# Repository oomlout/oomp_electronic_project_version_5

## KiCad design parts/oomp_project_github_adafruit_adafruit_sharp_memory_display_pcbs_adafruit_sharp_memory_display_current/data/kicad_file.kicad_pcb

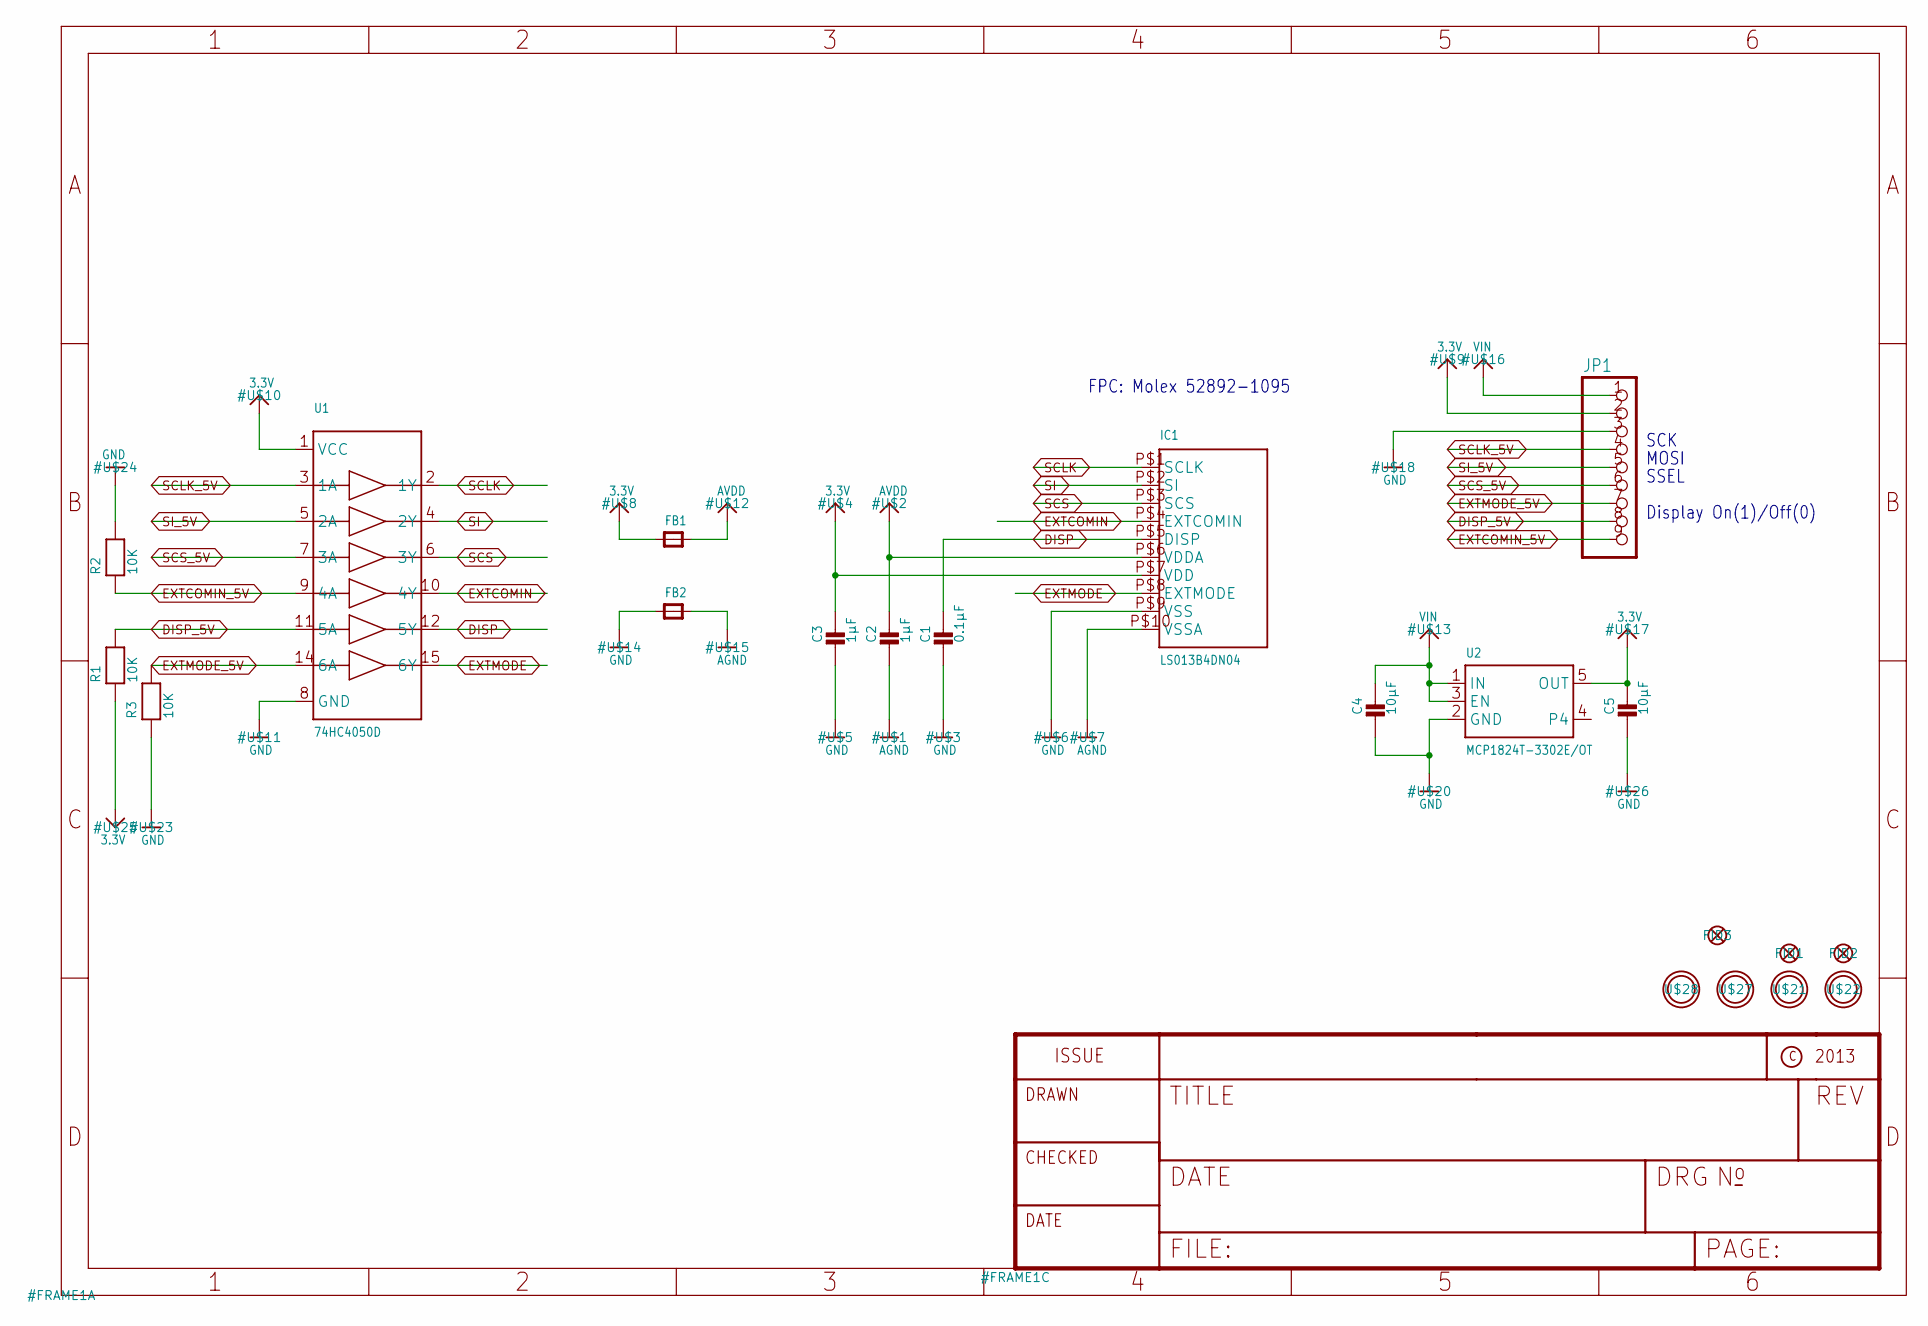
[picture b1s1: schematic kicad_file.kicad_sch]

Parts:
C1: 0.1µF; _0805
C2, C3: 1µF; _0805
C4, C5: 10µF; _0805
FB1, FB2: FERRITE_0805; _0805
FID1, FID2, FID3: FIDUCIAL""; FIDUCIAL_1MM
IC1: LS013B4DN04; FPC_10PIN_52892-1095
JP1: HEADER-1X970MIL; 1X09_ROUND_70
R1, R2, R3: 10K; _0805
U1: 74HC4050D; SOIC16
U2: MCP1824T-3302E/OT; SOT23-5
U$21, U$22, U$27, U$28: MOUNTINGHOLE3.0THIN; MOUNTINGHOLE_3.0_PLATEDTHIN

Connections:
3.3V: C3.1, C5.1, FB1.1, IC1.P$7 (VDD), JP1.2, R1.1, U1.1 (VCC), U2.5 (OUT)
AGND: C2.2, FB2.2, IC1.P$10 (VSSA)
AVDD: C2.1, FB1.2, IC1.P$6 (VDDA)
DISP: C1.1, IC1.P$5 (DISP), U1.12 (5Y)
DISP_5V: JP1.8, R1.2, U1.11 (5A)
EXTCOMIN: IC1.P$4 (EXTCOMIN), U1.10 (4Y)
EXTCOMIN_5V: JP1.9, R2.1, U1.9 (4A)
EXTMODE: IC1.P$8 (EXTMODE), U1.15 (6Y)
EXTMODE_5V: JP1.7, R3.2, U1.14 (6A)
GND: C1.2, C3.2, C4.2, C5.2, FB2.1, IC1.P$9 (VSS), JP1.3, R2.2, R3.1, U1.8 (GND), U2.2 (GND)
SCLK: IC1.P$1 (SCLK), U1.2 (1Y)
SCLK_5V: JP1.4, U1.3 (1A)
SCS: IC1.P$3 (SCS), U1.6 (3Y)
SCS_5V: JP1.6, U1.7 (3A)
SI: IC1.P$2 (SI), U1.4 (2Y)
SI_5V: JP1.5, U1.5 (2A)
VIN: C4.1, JP1.1, U2.1 (IN), U2.3 (EN)

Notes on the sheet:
MOSI
SSEL
FPC: Molex 52892-1095
SCK
Display On(1)/Off(0)

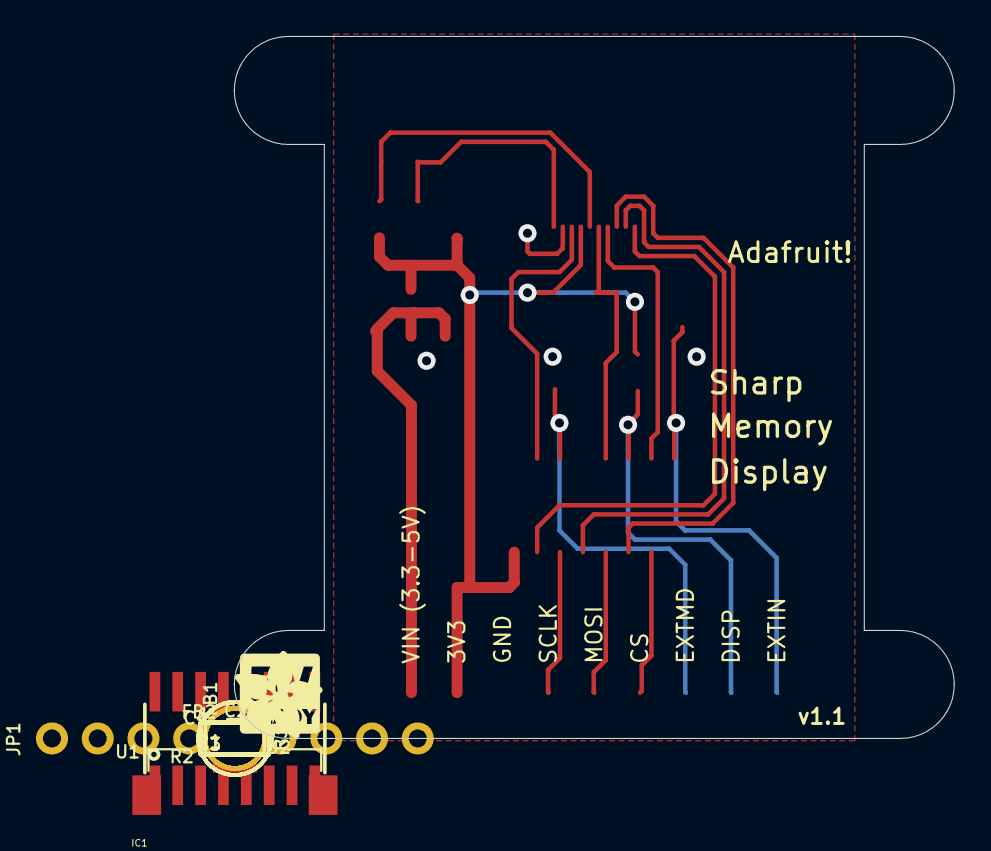
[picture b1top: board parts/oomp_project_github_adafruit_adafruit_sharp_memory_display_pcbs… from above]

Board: 16 copper layers, 40.0 x 39.0 mm, 23 parts (0 on the bottom side), 17 nets.

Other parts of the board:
U$19: LOGIC_5VREADY_5MM
U$29: ADAFRUIT_5MM

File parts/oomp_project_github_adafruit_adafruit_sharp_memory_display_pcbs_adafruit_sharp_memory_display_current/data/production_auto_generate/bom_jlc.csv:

Comment,Designator,Footprint,LCSC Part #
,JP1,Adafruit_SharpMemoryDisplay-import-fps:1X09_ROUND_70,C2932701
,"FB1,FB2",Adafruit_SharpMemoryDisplay-import-fps:_0805,
,U$29,Adafruit_SharpMemoryDisplay-import-fps:ADAFRUIT_5MM,
,U$19,Adafruit_SharpMemoryDisplay-import-fps:LOGIC_5VREADY_5MM,
0.1µF,C1,Adafruit_SharpMemoryDisplay-import-fps:_0805,
10K,"R1,R2,R3",Adafruit_SharpMemoryDisplay-import-fps:_0805,C17414
10µF,"C4,C5",Adafruit_SharpMemoryDisplay-import-fps:_0805,
1µF,"C2,C3",Adafruit_SharpMemoryDisplay-import-fps:_0805,
74HC4050D,U1,Adafruit_SharpMemoryDisplay-import-fps:SOIC16,
LS013B4DN04,IC1,Adafruit_SharpMemoryDisplay-import-fps:FPC_10PIN_52892-1095,
MCP1824T-3302E/OT,U2,Adafruit_SharpMemoryDisplay-import-fps:SOT23-5,

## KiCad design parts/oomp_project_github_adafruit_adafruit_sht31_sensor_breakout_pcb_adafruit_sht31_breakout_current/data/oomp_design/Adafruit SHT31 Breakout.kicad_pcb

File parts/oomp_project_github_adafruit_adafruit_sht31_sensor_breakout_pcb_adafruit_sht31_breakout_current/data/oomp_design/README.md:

# OOMP KiCad design copy

Open `Adafruit SHT31 Breakout.kicad_pro` (or the `.kicad_pcb` / `.kicad_sch`) in KiCad. Local OOMP libraries are under `libraries/`. Original inputs are preserved in [../original/](../original/).

Only verified unchanged installed KiCad defaults were renamed. Modified, custom, unmatched and unavailable items remain unchanged. Soldering variants are never swapped during conversion. Existing pad coordinates, nets and UUIDs are preserved.

See [conversion_report.yaml](conversion_report.yaml) for every conversion and skip. Copy this directory before editing; regeneration refuses to overwrite edited design files.

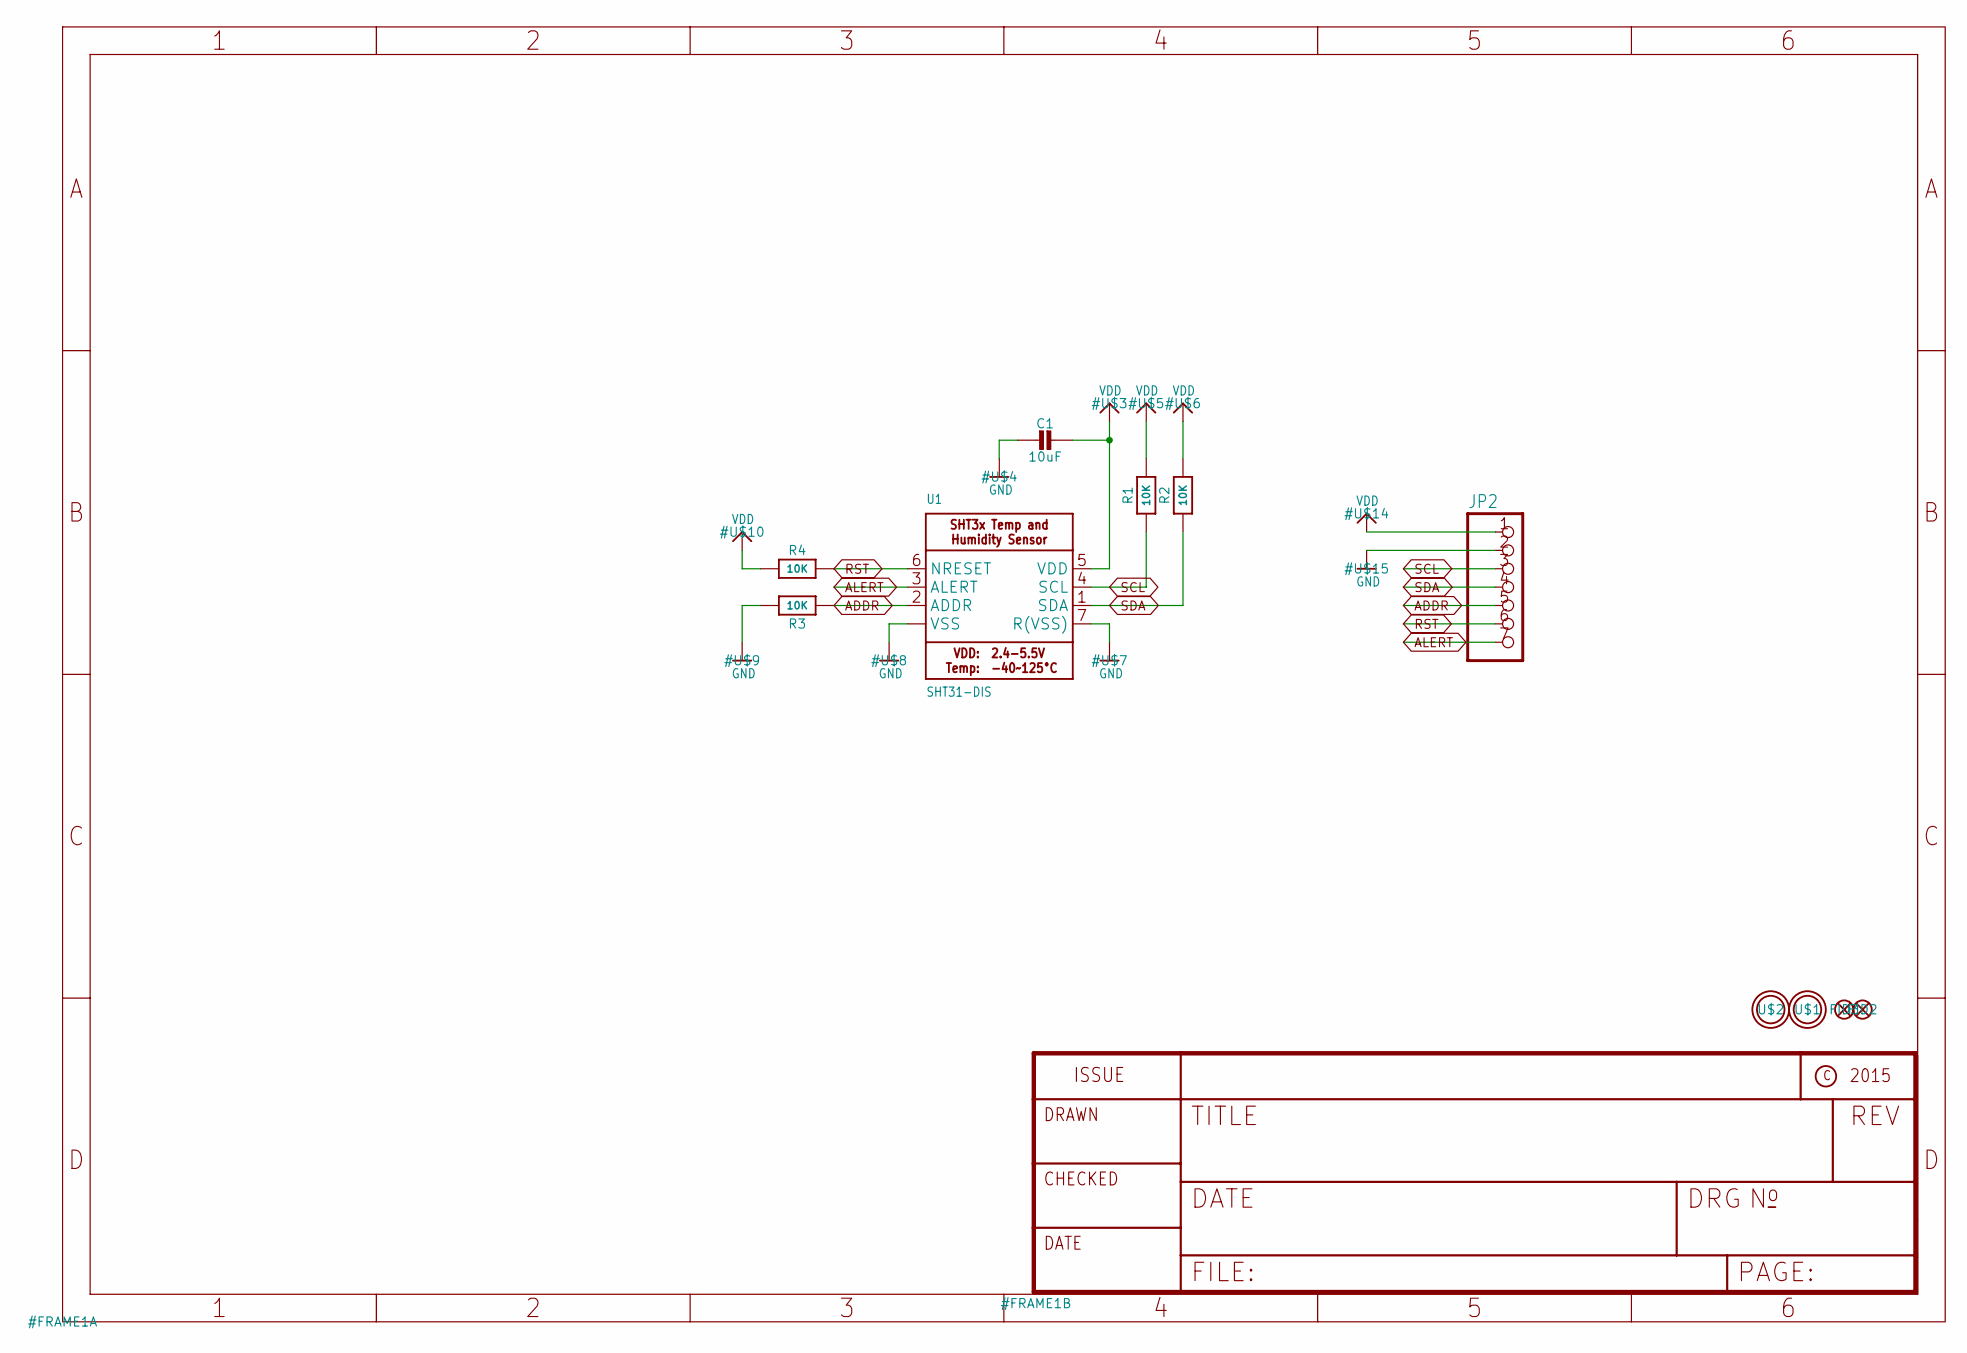
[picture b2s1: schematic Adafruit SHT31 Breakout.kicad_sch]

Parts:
C1: 10uF; 0805-NO
FID2, FID3: FIDUCIAL""; FIDUCIAL_1MM
JP2: HEADER-1X770MIL; 1X07_ROUND_70
R1, R2, R4: 10K; 0805-NO
R3: 10K; _0805MP
U1: SHT31-DIS; SHT3X
U$1, U$2: MOUNTINGHOLE2.5; MOUNTINGHOLE_2.5_PLATED

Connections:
ADDR: JP2.5, R3.1, U1.2 (ADDR)
ALERT: JP2.7, U1.3 (ALERT)
GND: C1.2, JP2.2, R3.2, U1.7 (R(VSS)), U1.8 (VSS), U1.THERMAL (VSS)
RST: JP2.6, R4.2, U1.6 (NRESET)
SCL: JP2.3, R1.1, U1.4 (SCL)
SDA: JP2.4, R2.1, U1.1 (SDA)
VDD: C1.1, JP2.1, R1.2, R2.2, R4.1, U1.5 (VDD)

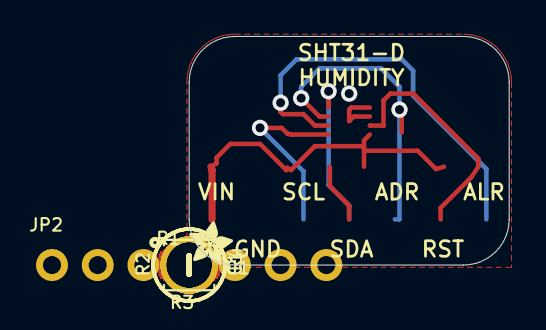
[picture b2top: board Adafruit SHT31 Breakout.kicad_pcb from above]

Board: 2 copper layers, 17.8 x 12.7 mm, 13 parts (1 on the bottom side), 7 nets.

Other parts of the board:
U$11: PCBFEAT-REV-040
U$13: ADAFRUIT_2.5MM

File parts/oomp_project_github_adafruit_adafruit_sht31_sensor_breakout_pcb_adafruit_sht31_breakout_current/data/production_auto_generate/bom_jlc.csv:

Comment,Designator,Footprint,LCSC Part #
,JP2,Adafruit SHT31 Breakout-import-fps:1X07_ROUND_70,C7501585
,U$13,Adafruit SHT31 Breakout-import-fps:ADAFRUIT_2.5MM,
,U$11,Adafruit SHT31 Breakout-import-fps:PCBFEAT-REV-040,
10K,"R1,R2,R4",Adafruit SHT31 Breakout-import-fps:0805-NO,C17414
10K,R3,Adafruit SHT31 Breakout-import-fps:_0805MP,C17414
10uF,C1,Adafruit SHT31 Breakout-import-fps:0805-NO,
SHT31-DIS,U1,Adafruit SHT31 Breakout-import-fps:SHT3X,

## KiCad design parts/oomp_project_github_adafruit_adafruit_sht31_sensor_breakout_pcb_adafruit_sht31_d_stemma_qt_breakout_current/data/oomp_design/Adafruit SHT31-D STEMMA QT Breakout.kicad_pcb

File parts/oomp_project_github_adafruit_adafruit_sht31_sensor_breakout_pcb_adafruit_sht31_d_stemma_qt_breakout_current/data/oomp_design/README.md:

# OOMP KiCad design copy

Open `Adafruit SHT31-D STEMMA QT Breakout.kicad_pro` (or the `.kicad_pcb` / `.kicad_sch`) in KiCad. Local OOMP libraries are under `libraries/`. Original inputs are preserved in [../original/](../original/).

Only verified unchanged installed KiCad defaults were renamed. Modified, custom, unmatched and unavailable items remain unchanged. Soldering variants are never swapped during conversion. Existing pad coordinates, nets and UUIDs are preserved.

See [conversion_report.yaml](conversion_report.yaml) for every conversion and skip. Copy this directory before editing; regeneration refuses to overwrite edited design files.

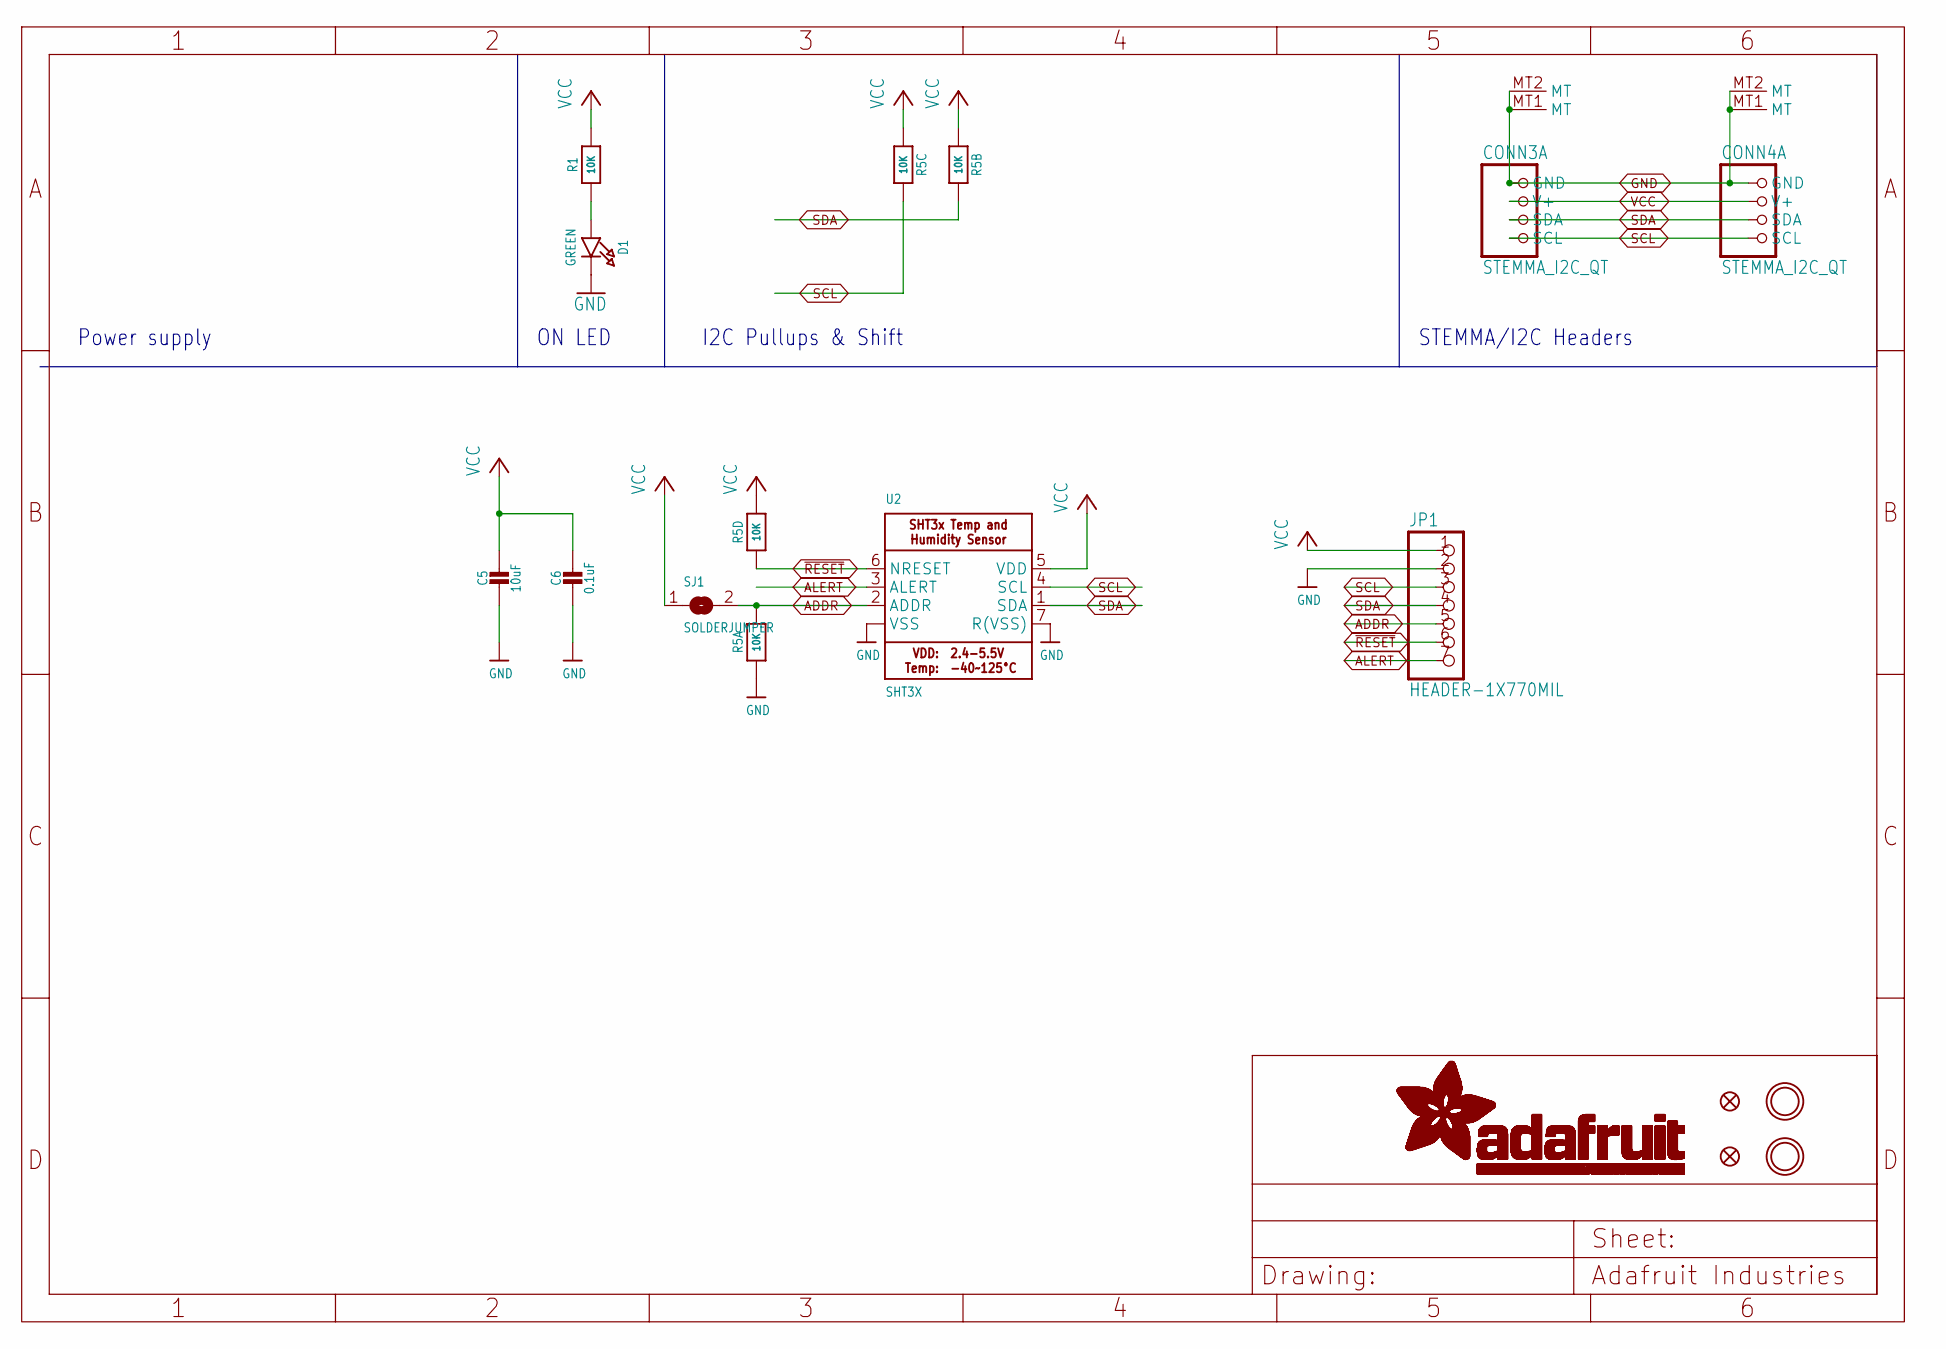
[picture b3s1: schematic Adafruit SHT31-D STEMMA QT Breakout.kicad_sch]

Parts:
C5: 10uF; 0805-NO
C6: 0.1uF; 0603-NO
CONN3, CONN4: STEMMA_I2C_QT; JST_SH4
D1: GREEN; CHIPLED_0603_NOOUTLINE
FID3, FID4: FIDUCIAL_1MM
JP1: HEADER-1X770MIL; 1X07_ROUND_70
R1: 10K; 0603-NO
R5: 10K; RESPACK_4X0603
SJ1: SOLDERJUMPER; SOLDERJUMPER_ARROW_NOPASTE
U2: SHT3X
U$19, U$20: MOUNTINGHOLE2.5; MOUNTINGHOLE_2.5_PLATED

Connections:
ADDR: JP1.5, R5.8 (2), SJ1.2, U2.2 (ADDR)
ALERT: JP1.7, U2.3 (ALERT)
GND: C5.2, C6.2, CONN3.1 (GND), CONN3.MT1 (MT), CONN3.MT2 (MT), CONN4.1 (GND), CONN4.MT1 (MT), CONN4.MT2 (MT), D1.C, JP1.2, R5.1, U2.7 (R(VSS)), U2.8 (VSS), U2.THERMAL (VSS)
unnamed: D1.A, R1.1
SCL: CONN3.4 (SCL), CONN4.4 (SCL), JP1.3, R5.6 (2), U2.4 (SCL)
SDA: CONN3.3 (SDA), CONN4.3 (SDA), JP1.4, R5.7 (2), U2.1 (SDA)
VCC: C5.1, C6.1, CONN3.2 (V+), CONN4.2 (V+), JP1.1, R1.2, R5.2 (1), R5.3 (1), R5.5 (2), SJ1.1, U2.5 (VDD)
~RESET: JP1.6, R5.4 (1), U2.6 (NRESET)

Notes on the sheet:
STEMMA/I2C Headers
Power supply
I2C Pullups & Shift
ON LED

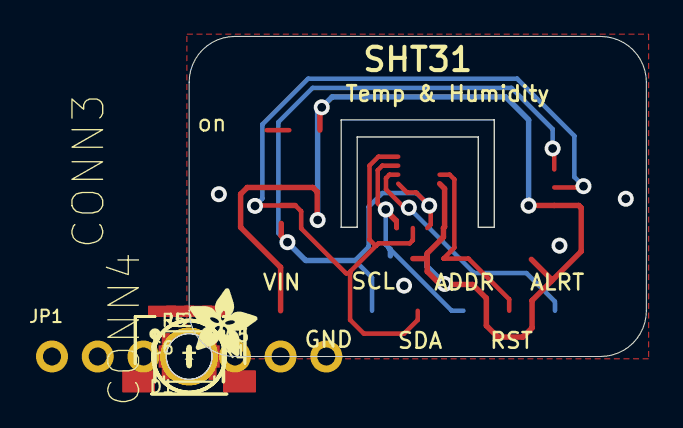
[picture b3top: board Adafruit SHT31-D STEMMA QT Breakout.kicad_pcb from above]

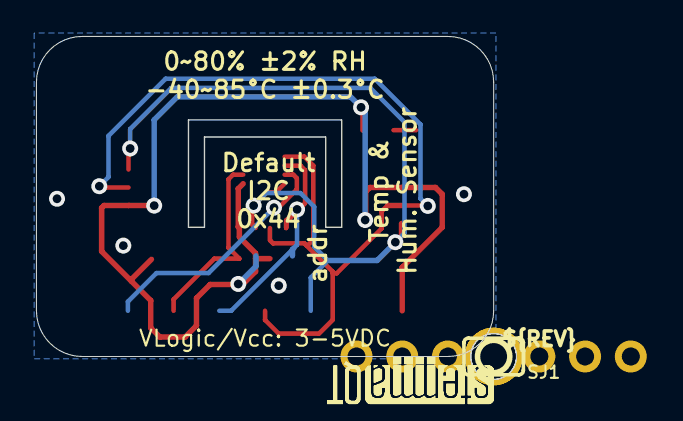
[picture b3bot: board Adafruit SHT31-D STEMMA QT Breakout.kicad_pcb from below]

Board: 2 copper layers, 25.4 x 17.8 mm, 20 parts (4 on the bottom side), 8 nets.

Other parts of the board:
U$28: ADAFRUIT_3.5MM
U$29: PCBFEAT-REV-040
U$30, U$31: STEMMAQT
UNK_HOLE_0: dummyfp0
UNK_HOLE_1: dummyfp1

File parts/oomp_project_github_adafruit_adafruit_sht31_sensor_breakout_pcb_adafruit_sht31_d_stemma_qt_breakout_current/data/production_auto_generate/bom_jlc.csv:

Comment,Designator,Footprint,LCSC Part #
,JP1,Adafruit SHT31-D STEMMA QT Breakout-import-fps:1X07_ROUND_70,C7501585
,U$28,Adafruit SHT31-D STEMMA QT Breakout-import-fps:ADAFRUIT_3.5MM,
,U$29,Adafruit SHT31-D STEMMA QT Breakout-import-fps:PCBFEAT-REV-040,
,U2,Adafruit SHT31-D STEMMA QT Breakout-import-fps:SHT3X,
,"U$30,U$31",Adafruit SHT31-D STEMMA QT Breakout-import-fps:STEMMAQT,
0.1uF,C6,Adafruit SHT31-D STEMMA QT Breakout-import-fps:0603-NO,C14663
10K,R1,Adafruit SHT31-D STEMMA QT Breakout-import-fps:0603-NO,C98220
10K,R5,Adafruit SHT31-D STEMMA QT Breakout-import-fps:RESPACK_4X0603,C98220
10uF,C5,Adafruit SHT31-D STEMMA QT Breakout-import-fps:0805-NO,
GREEN,D1,Adafruit SHT31-D STEMMA QT Breakout-import-fps:CHIPLED_0603_NOOUTLINE,
STEMMA_I2C_QT,"CONN3,CONN4",Adafruit SHT31-D STEMMA QT Breakout-import-fps:JST_SH4,C160404

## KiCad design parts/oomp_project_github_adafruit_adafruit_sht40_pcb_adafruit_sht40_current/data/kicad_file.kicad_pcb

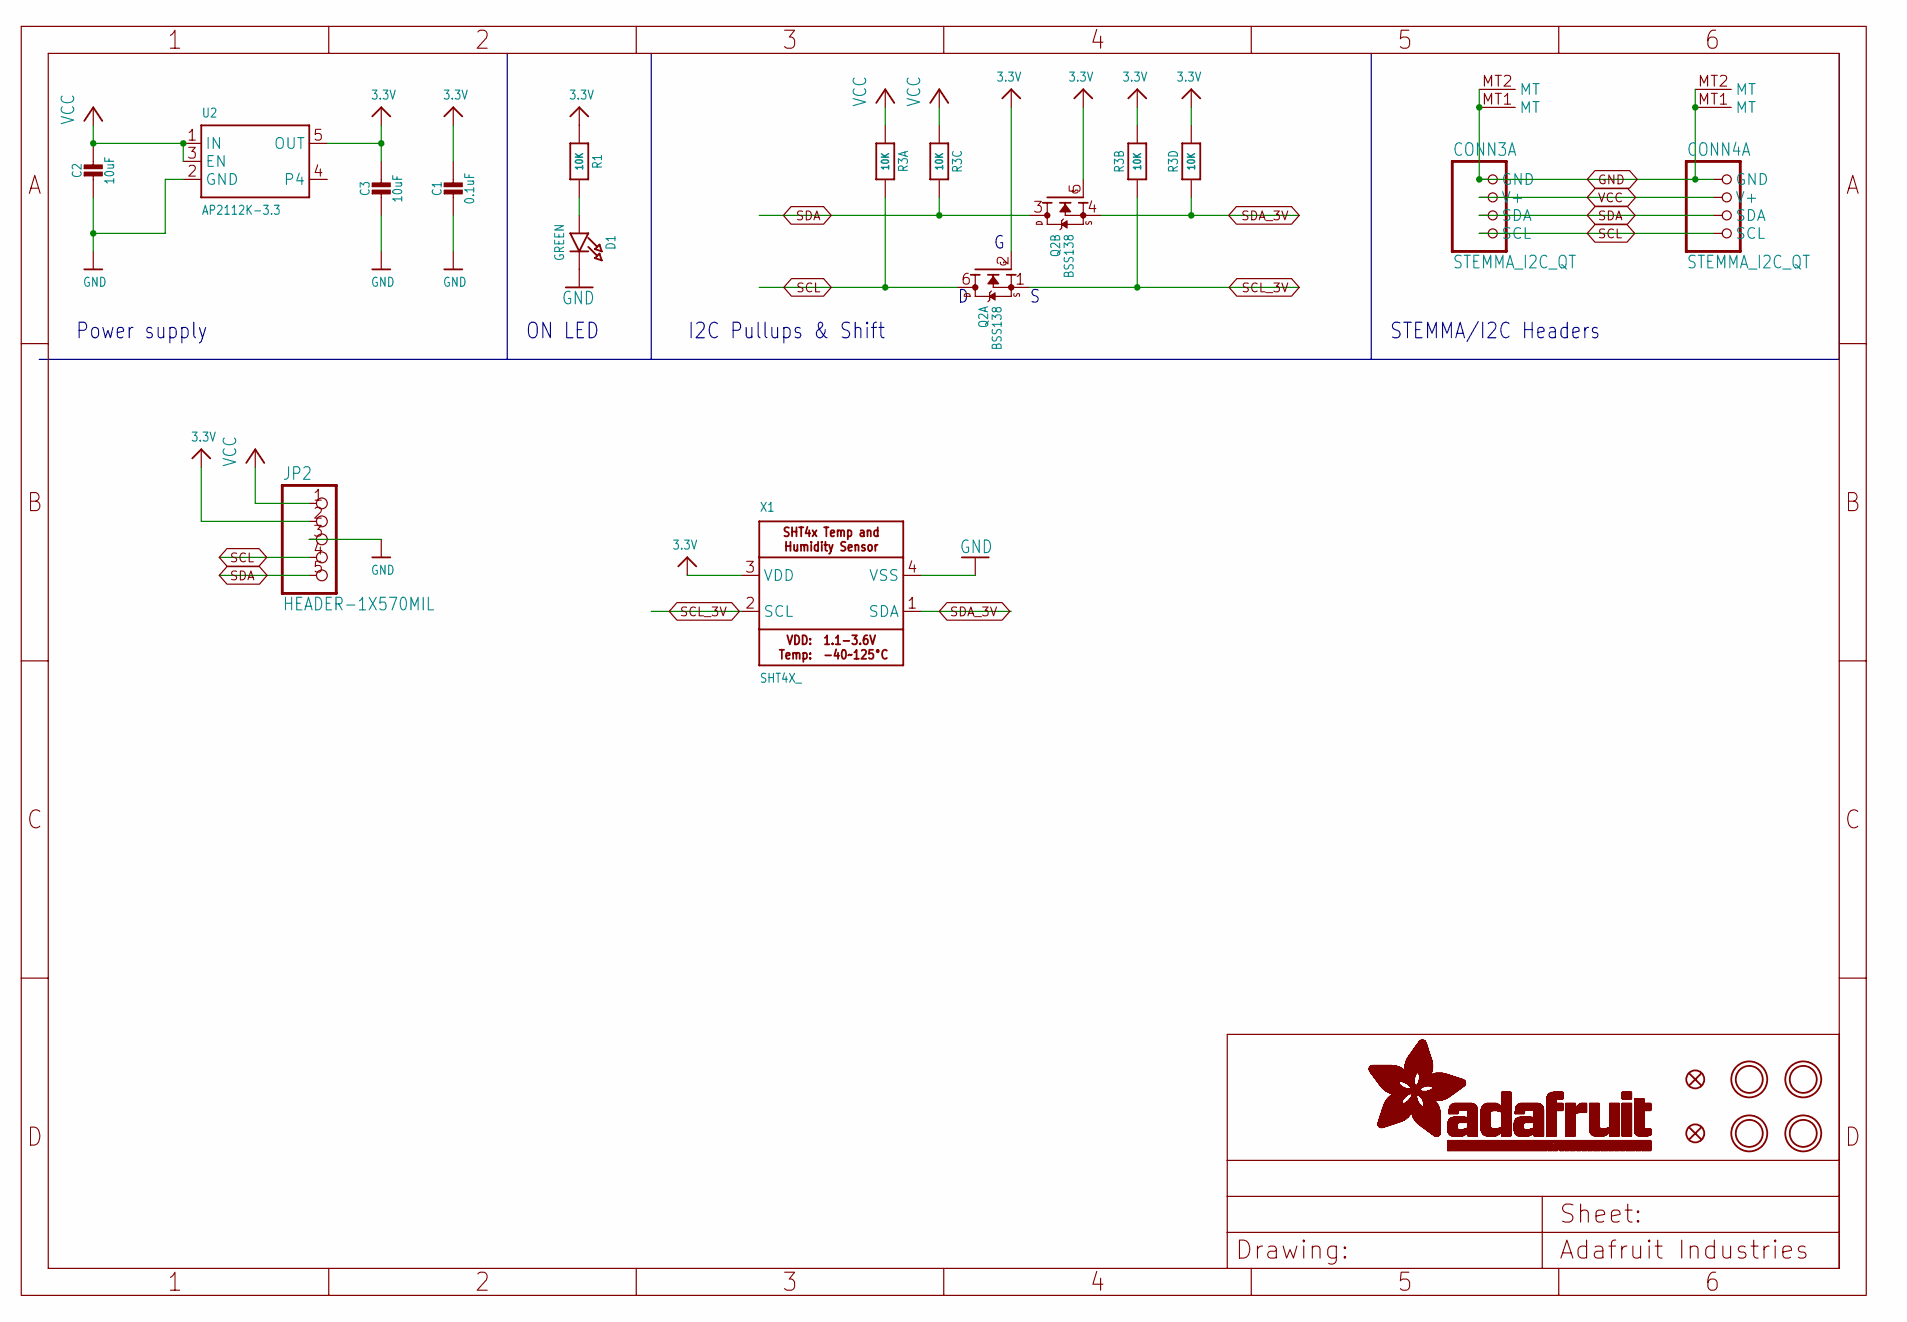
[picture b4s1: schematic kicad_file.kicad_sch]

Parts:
C1: 0.1uF; 0603-NO
C2, C3: 10uF; 0805-NO
CONN3, CONN4: STEMMA_I2C_QT; JST_SH4
D1: GREEN; CHIPLED_0603_NOOUTLINE
FID3, FID4: FIDUCIAL_1MM
JP2: HEADER-1X570MIL; 1X05_ROUND_70
Q2: BSS138; SOT363
R1: 10K; 0603-NO
R3: 10K; RESPACK_4X0603
U2: AP2112K-3.3; SOT23-5
U$1, U$17, U$19, U$21: MOUNTINGHOLE2.5; MOUNTINGHOLE_2.5_PLATED
X1: SHT4X_; SHT4X

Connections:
3.3V: C1.1, C3.1, JP2.2, Q2.2 (G), Q2.5 (G), R1.1, R3.2 (1), R3.4 (1), U2.5 (OUT), X1.3 (VDD)
GND: C1.2, C2.2, C3.2, CONN3.1 (GND), CONN3.MT1 (MT), CONN3.MT2 (MT), CONN4.1 (GND), CONN4.MT1 (MT), CONN4.MT2 (MT), D1.C, JP2.3, U2.2 (GND), X1.4 (VSS)
unnamed: D1.A, R1.2
SCL: CONN3.4 (SCL), CONN4.4 (SCL), JP2.4, Q2.6 (D), R3.8 (2)
SCL_3V: Q2.1 (S), R3.7 (2), X1.2 (SCL)
SDA: CONN3.3 (SDA), CONN4.3 (SDA), JP2.5, Q2.3 (D), R3.6 (2)
SDA_3V: Q2.4 (S), R3.5 (2), X1.1 (SDA)
VCC: C2.1, CONN3.2 (V+), CONN4.2 (V+), JP2.1, R3.1, R3.3 (1), U2.1 (IN), U2.3 (EN)

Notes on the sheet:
STEMMA/I2C Headers
I2C Pullups & Shift
Power supply
ON LED

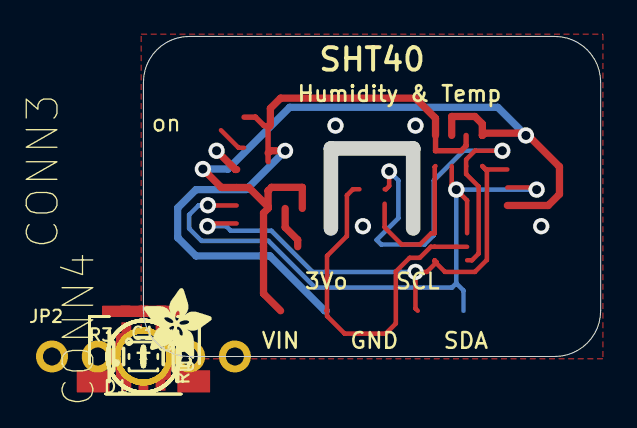
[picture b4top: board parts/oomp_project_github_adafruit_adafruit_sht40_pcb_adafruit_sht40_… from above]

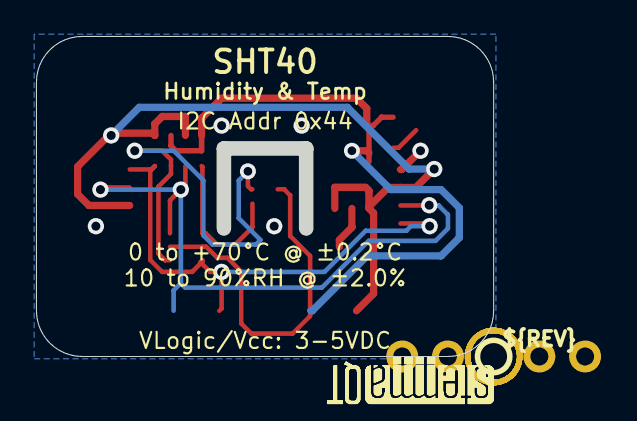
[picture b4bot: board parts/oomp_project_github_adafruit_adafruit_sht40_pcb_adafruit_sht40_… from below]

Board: 2 copper layers, 25.4 x 17.8 mm, 22 parts (3 on the bottom side), 8 nets.

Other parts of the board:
U$22: ADAFRUIT_3.5MM
U$25: PCBFEAT-REV-040
U$30, U$31: STEMMAQT

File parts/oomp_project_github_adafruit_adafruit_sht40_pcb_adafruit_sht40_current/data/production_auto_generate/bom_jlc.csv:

Comment,Designator,Footprint,LCSC Part #
,JP2,Adafruit SHT40-import-fps:1X05_ROUND_70,C42431835
,U$22,Adafruit SHT40-import-fps:ADAFRUIT_3.5MM,
,U$25,Adafruit SHT40-import-fps:PCBFEAT-REV-040,
,"U$30,U$31",Adafruit SHT40-import-fps:STEMMAQT,
0.1uF,C1,Adafruit SHT40-import-fps:0603-NO,C14663
10K,R1,Adafruit SHT40-import-fps:0603-NO,C98220
10K,R3,Adafruit SHT40-import-fps:RESPACK_4X0603,C98220
10uF,"C2,C3",Adafruit SHT40-import-fps:0805-NO,
AP2112K-3.3,U2,Adafruit SHT40-import-fps:SOT23-5,
BSS138,Q2,Adafruit SHT40-import-fps:SOT363,
GREEN,D1,Adafruit SHT40-import-fps:CHIPLED_0603_NOOUTLINE,
SHT4X_,X1,Adafruit SHT40-import-fps:SHT4X,
STEMMA_I2C_QT,"CONN3,CONN4",Adafruit SHT40-import-fps:JST_SH4,C160404

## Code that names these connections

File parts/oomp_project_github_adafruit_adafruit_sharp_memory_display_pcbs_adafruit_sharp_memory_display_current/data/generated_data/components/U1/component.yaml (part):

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      connected_to:
      - reference: IC1
        pin_number: P$3
        pin_name: SCS
    - number: '7'
      name: 3A
      electrical_type: bidirectional
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      connected_to:
      - reference: IC1
        pin_number: P$4
        pin_name: EXTCOMIN
    - number: '11'
      name: 5A
      electrical_type: bidirectional
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        pin_name: P$1
      - reference: IC1
        pin_number: P$5
        pin_name: DISP
    - number: '14'
      name: 6A
      electrical_type: bidirectional
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      connected_to:
      - reference: IC1
        pin_number: P$8
        pin_name: EXTMODE
    size:
      local_graphics:
        measurement: symbol graphics only; excludes pins, properties, and text
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    pin_name: SI
  - reference: IC1
    pin_number: P$3
    pin_name: SCS
  - reference: IC1
    pin_number: P$4
    pin_name: EXTCOMIN
  - reference: IC1
    pin_number: P$5
    pin_name: DISP
  - reference: IC1
    pin_number: P$7
    pin_name: VDD
  - reference: IC1
    pin_number: P$8
    pin_name: EXTMODE
  - reference: IC1
    pin_number: P$9
    pin_name: VSS
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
